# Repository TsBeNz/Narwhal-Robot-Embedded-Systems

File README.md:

# Module89-Frab5-G3
Electronics &amp; Embedded Systems

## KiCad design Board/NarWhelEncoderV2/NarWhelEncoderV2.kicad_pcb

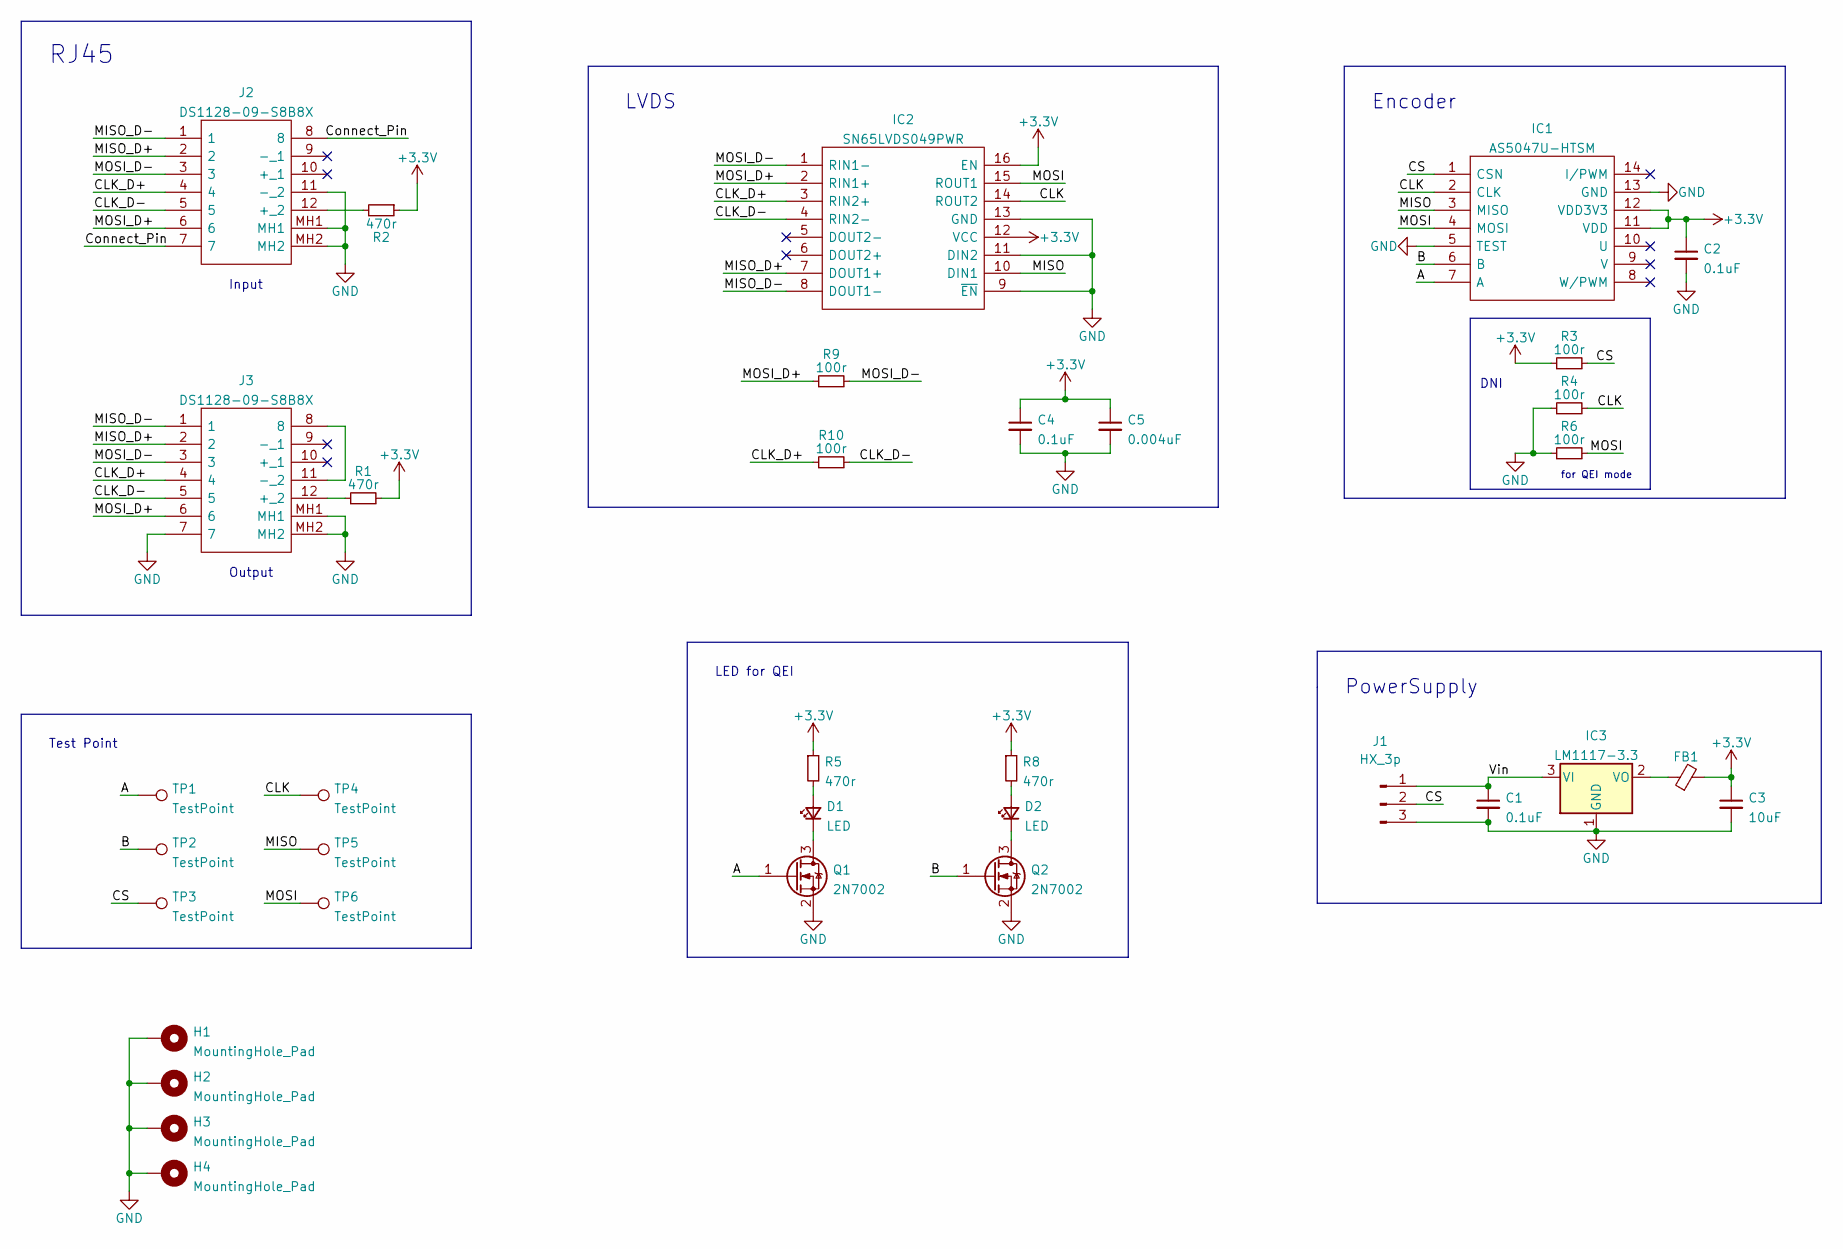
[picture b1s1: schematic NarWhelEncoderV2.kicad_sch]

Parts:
C1, C2, C4: 0.1uF; C_0603_1608Metric_Pad1.08x0.95mm_HandSolder
C3: 10uF; C_0603_1608Metric_Pad1.08x0.95mm_HandSolder
C5: 0.004uF; C_0603_1608Metric_Pad1.08x0.95mm_HandSolder
D1, D2: LED; LED_0603_1608Metric_Pad1.05x0.95mm_HandSolder
FB1: FerriteBead_Small; L_0603_1608Metric_Pad1.05x0.95mm_HandSolder
H1, H2, H3, H4: MountingHole_Pad; MountingHole_3.2mm_M3_Pad_Via
IC1: AS5047U-HTSM; SOP65P640X120-14N; Manufacturer_Part_Number AS5047U-HTSM; Mouser Part Number 985-AS5047U-HTSM
IC2: SN65LVDS049PWR; SOP65P640X120-16N; Manufacturer_Part_Number SN65LVDS049PWR; Mouser Part Number 595-SN65LVDS049PWR
IC3: LM1117-3.3; SOT-223-3_TabPin2
J1: HX_3p; JST_XH_B3B-XH-A_1x03_P2.50mm_Vertical
J2, J3: DS1128-09-S8B8X; DS112809S8B8X; Manufacturer_Part_Number DS1128-09-S8B8X
Q1, Q2: 2N7002; SOT-23_Handsoldering
R1, R2, R5, R8: 470r; R_0603_1608Metric_Pad0.98x0.95mm_HandSolder
R3, R4, R6, R9, R10: 100r; R_0603_1608Metric_Pad0.98x0.95mm_HandSolder
TP1, TP2, TP3, TP4, TP5, TP6: TestPoint; TestPoint_Pad_D1.5mm

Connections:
+3V3: C2.1, C3.1, C4.1, C5.1, FB1.2, IC1.11 (VDD), IC1.12 (VDD3V3), IC2.12 (VCC), IC2.16 (EN), R1.2, R2.1, R3.1, R5.1, R8.1
/A: IC1.7 (A), Q1.1 (G), TP1.1
/B: IC1.6 (B), Q2.1 (G), TP2.1
/CLK: IC1.2 (CLK), IC2.14 (ROUT2), R4.2, TP4.1
/CLK_D+: IC2.3 (RIN2+), J2.4, J3.4, R10.1
/CLK_D-: IC2.4 (RIN2-), J2.5, J3.5, R10.2
/CS: IC1.1 (CSN), J1.2, R3.2, TP3.1
/Connect_Pin: J2.7, J2.8
/MISO: IC1.3 (MISO), IC2.10 (DIN1), TP5.1
/MISO_D+: IC2.7 (DOUT1+), J2.2, J3.2
/MISO_D-: IC2.8 (DOUT1-), J2.1, J3.1
/MOSI: IC1.4 (MOSI), IC2.15 (ROUT1), R6.2, TP6.1
/MOSI_D+: IC2.2 (RIN1+), J2.6, J3.6, R9.1
/MOSI_D-: IC2.1 (RIN1-), J2.3, J3.3, R9.2
/Vin: C1.1, IC3.3 (VI), J1.1
GND: C1.2, C2.2, C3.2, C4.2, C5.2, H1.1, H2.1, H3.1, H4.1, IC1.5 (TEST), IC1.13 (GND), IC2.9 (~EN), IC2.11 (DIN2), IC2.13 (GND), IC3.1 (GND), J1.3, J2.11 (-_2), J2.MH1, J2.MH2, J3.7, J3.MH1, J3.MH2, Q1.2 (S), Q2.2 (S), R4.1, R6.1
unnamed: D1.1 (K), Q1.3 (D)
unnamed: D1.2 (A), R5.2
unnamed: D2.1 (K), Q2.3 (D)
unnamed: D2.2 (A), R8.2
unnamed: FB1.1, IC3.2 (VO)
unnamed: J2.12 (+_2), R2.2
unnamed: J3.8, J3.11 (-_2)
unnamed: J3.12 (+_2), R1.1

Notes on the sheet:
LED for QEI
Output
Test Point
Encoder
RJ45
Input
LVDS
PowerSupply
DNI
for QEI mode

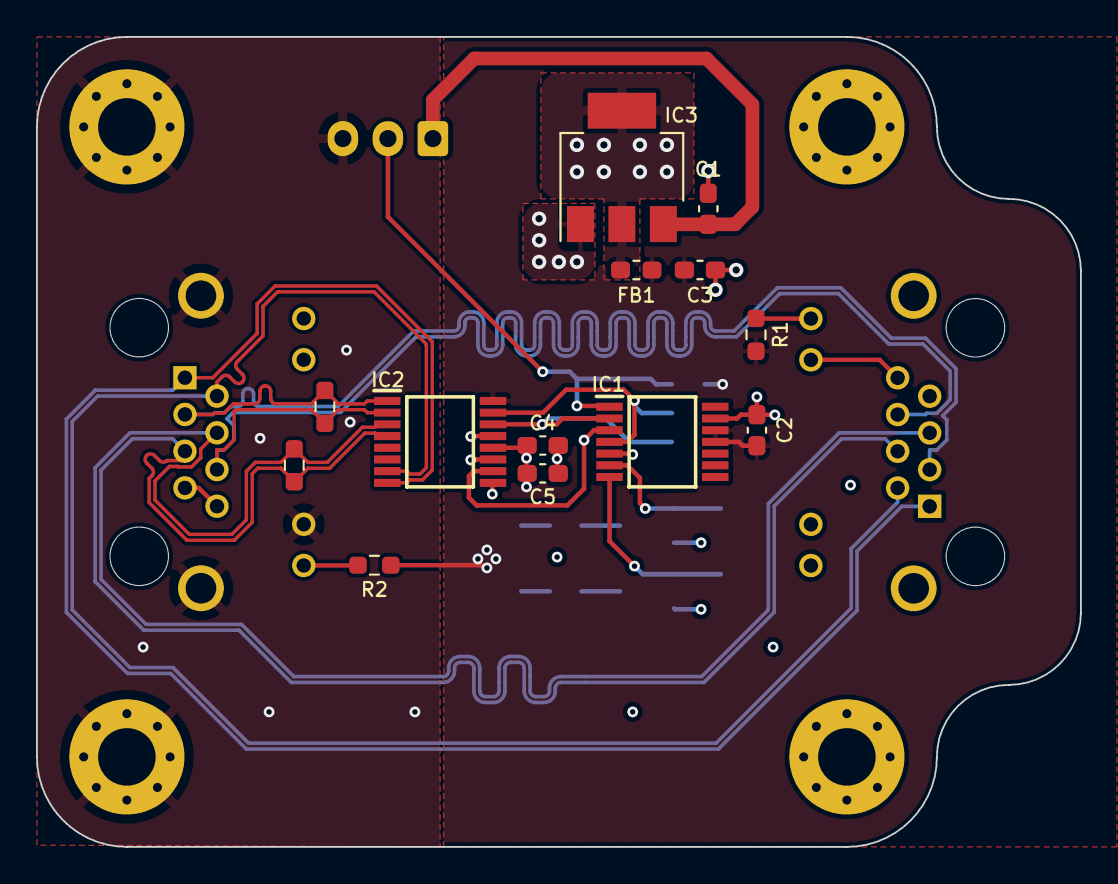
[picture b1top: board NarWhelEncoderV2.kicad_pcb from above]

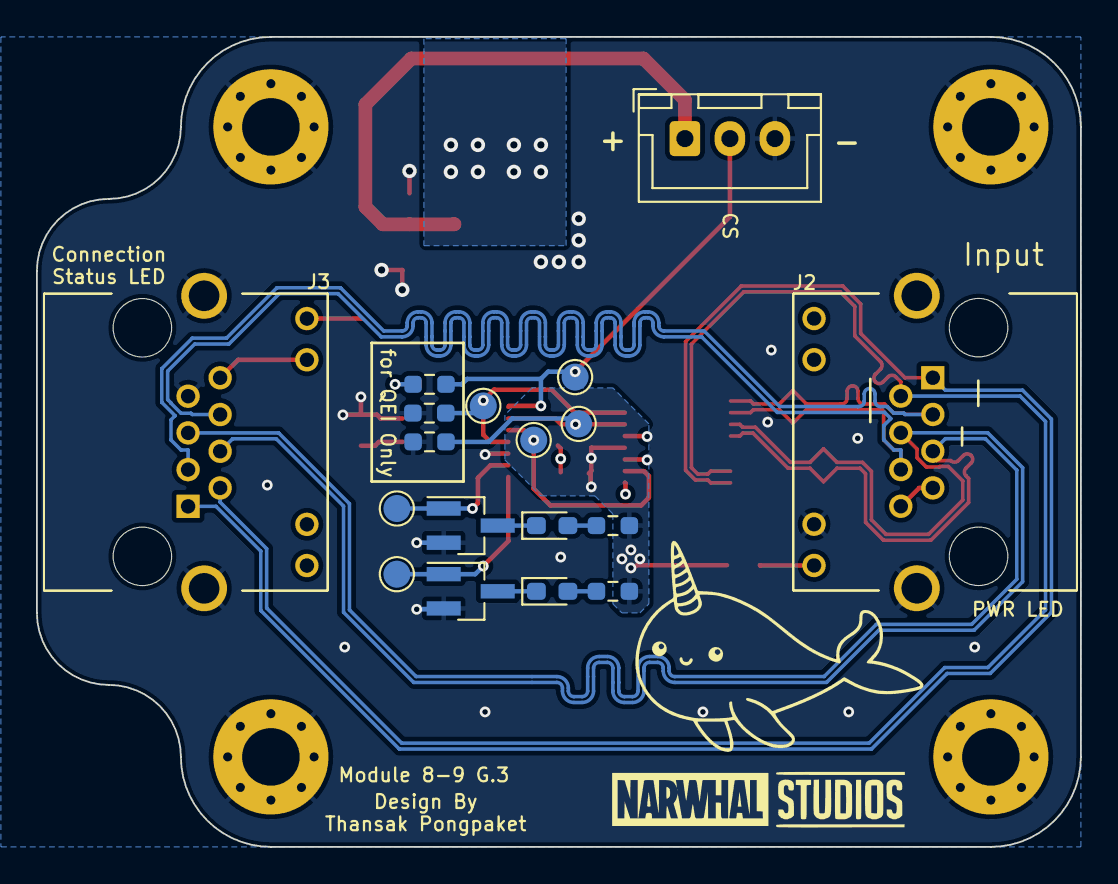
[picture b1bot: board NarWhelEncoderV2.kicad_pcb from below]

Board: 4 copper layers, 58.0 x 45.0 mm, 35 parts (18 on the bottom side), 24 nets.

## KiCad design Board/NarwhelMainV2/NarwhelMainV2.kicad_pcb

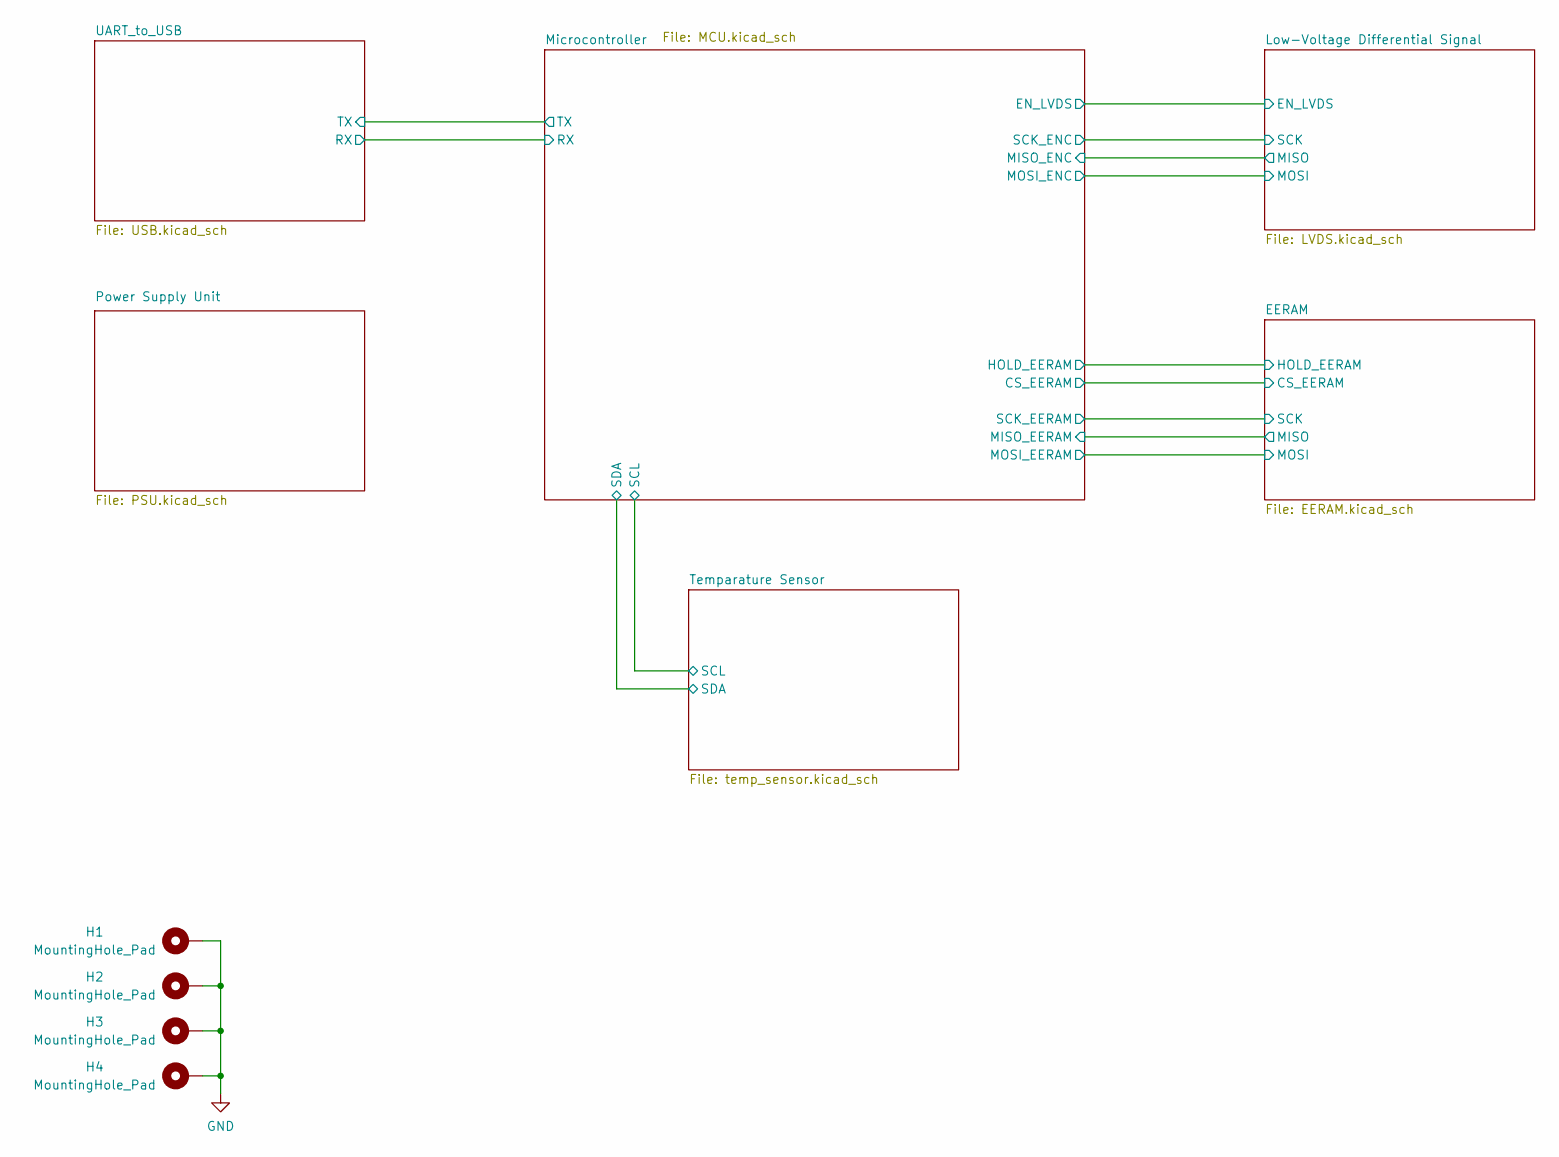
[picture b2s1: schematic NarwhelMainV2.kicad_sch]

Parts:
H1, H2, H3, H4: MountingHole_Pad; MountingHole_3.2mm_M3_Pad_Via

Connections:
GND: H1.1, H2.1, H3.1, H4.1; also elsewhere on the board

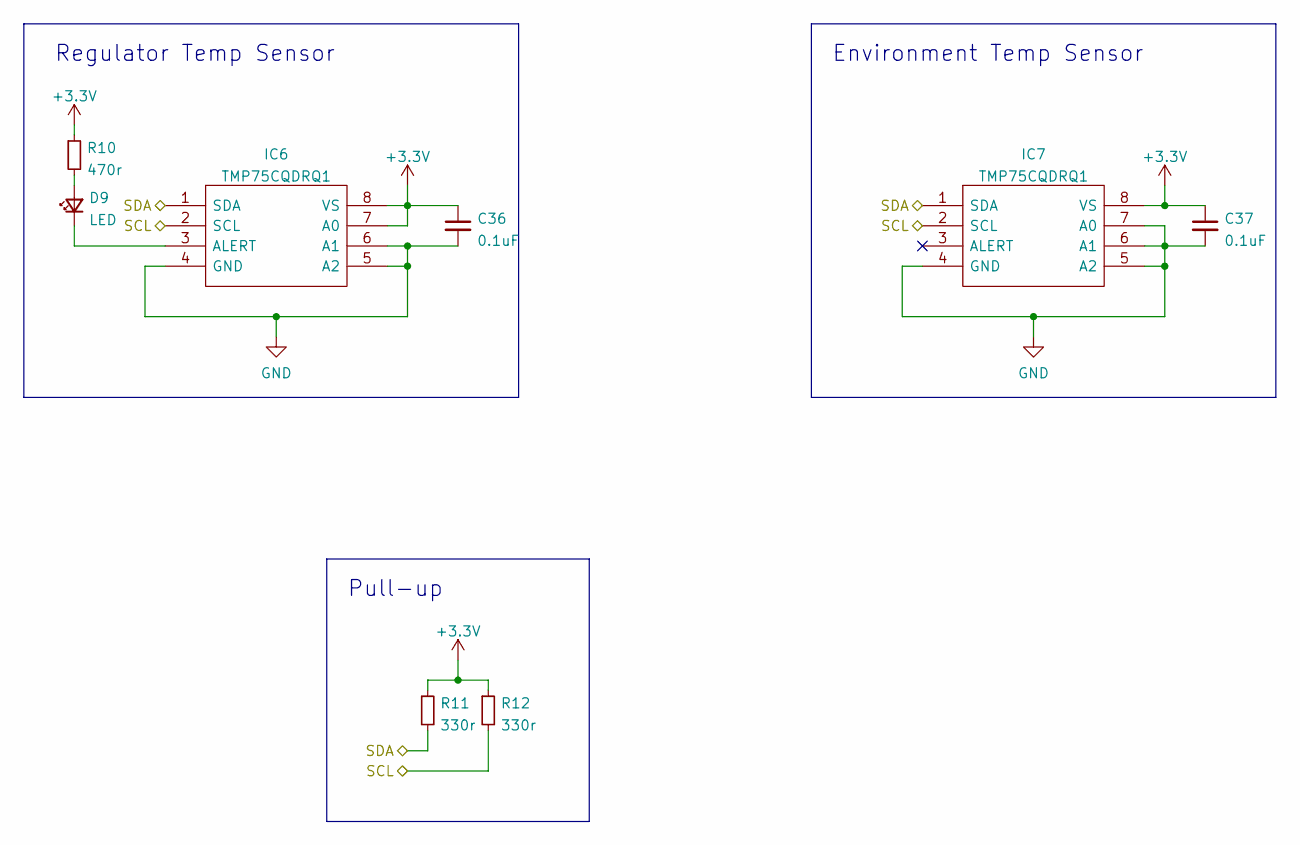
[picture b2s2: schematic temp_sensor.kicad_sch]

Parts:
C36, C37: 0.1uF; C_0603_1608Metric_Pad1.08x0.95mm_HandSolder
D9: LED; LED_0603_1608Metric_Pad1.05x0.95mm_HandSolder
IC6, IC7: TMP75CQDRQ1; SOIC127P600X175-8N; Manufacturer_Part_Number TMP75CQDRQ1; Mouser Part Number 595-TMP75CQDRQ1
R10: 470r; R_0603_1608Metric_Pad0.98x0.95mm_HandSolder
R11, R12: 330r; R_0603_1608Metric_Pad0.98x0.95mm_HandSolder

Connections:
+3V3: C36.1, C37.1, IC6.7 (A0), IC6.8 (VS), IC7.8 (VS), R10.1, R11.1, R12.1; also elsewhere on the board
/Microcontroller/SCL: IC6.2 (SCL), IC7.2 (SCL), R12.2; also elsewhere on the board
/Microcontroller/SDA: IC6.1 (SDA), IC7.1 (SDA), R11.2; also elsewhere on the board
GND: C36.2, C37.2, IC6.4 (GND), IC6.5 (A2), IC6.6 (A1), IC7.4 (GND), IC7.5 (A2), IC7.6 (A1), IC7.7 (A0); also elsewhere on the board
unnamed: D9.1 (K), IC6.3 (ALERT)
unnamed: D9.2 (A), R10.2

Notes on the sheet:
Regulator Temp Sensor
Environment Temp Sensor
Pull-up

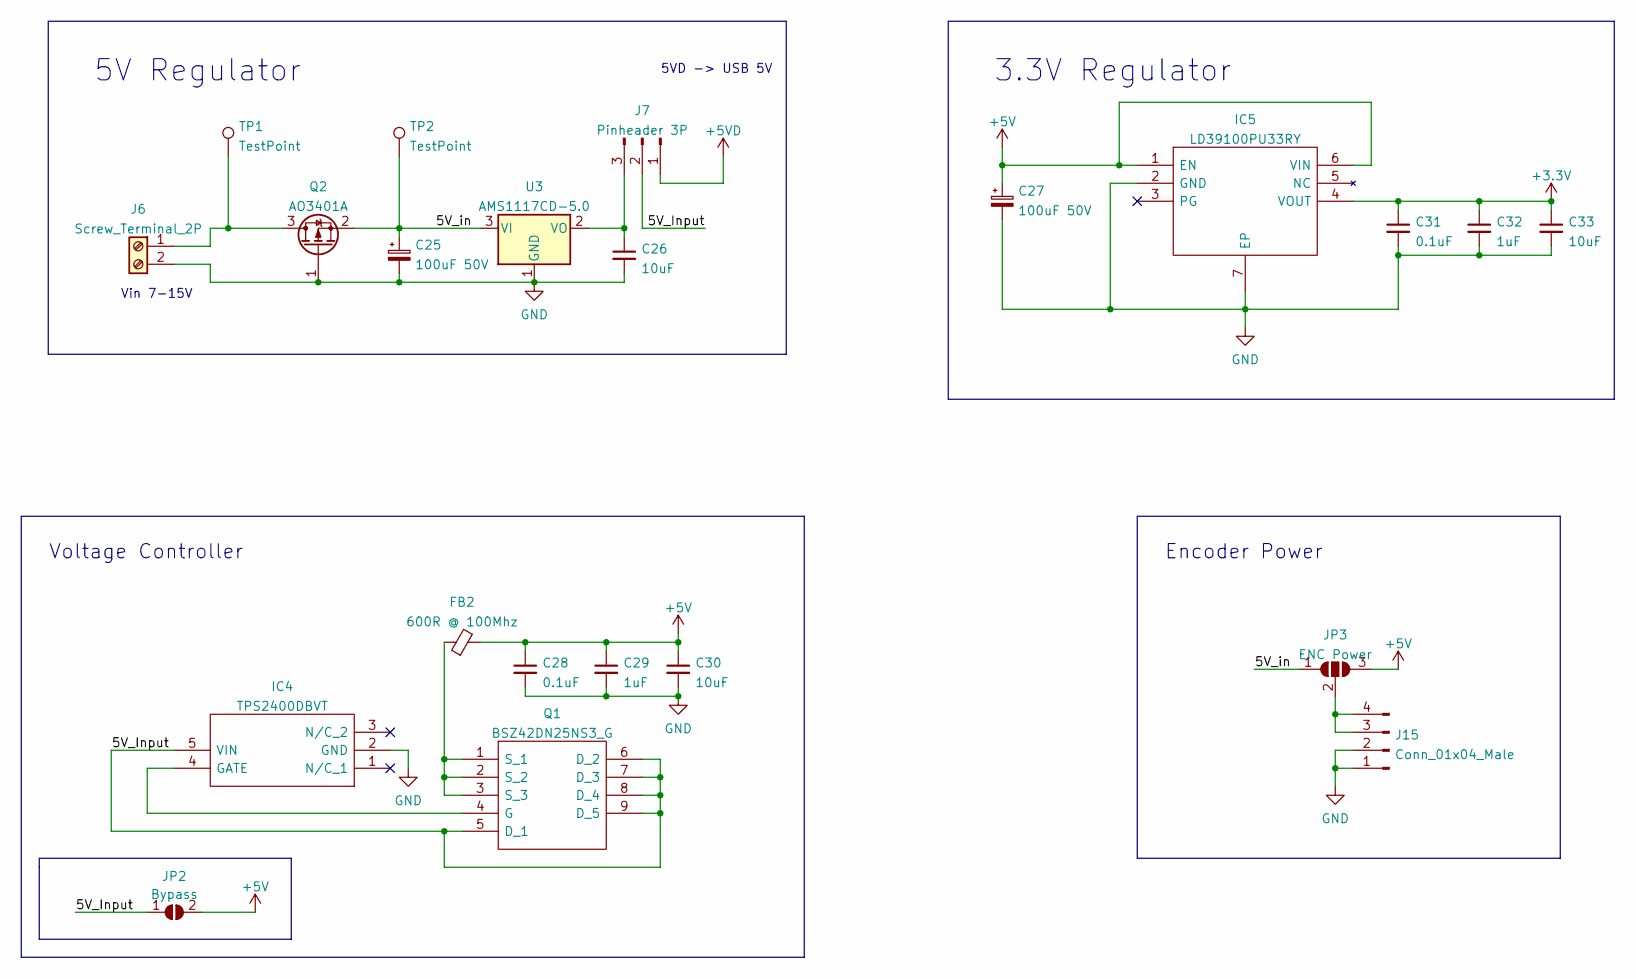
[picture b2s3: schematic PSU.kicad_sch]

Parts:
C25, C27: 100uF 50V; CP_Elec_6.3x5.4_Nichicon
C26, C30, C33: 10uF; C_0603_1608Metric_Pad1.08x0.95mm_HandSolder
C28, C31: 0.1uF; C_0603_1608Metric_Pad1.08x0.95mm_HandSolder
C29, C32: 1uF; C_0603_1608Metric_Pad1.08x0.95mm_HandSolder
FB2: 600R @ 100Mhz; L_0603_1608Metric_Pad1.05x0.95mm_HandSolder
IC4: TPS2400DBVT; SOT95P280X145-5N; Manufacturer_Part_Number TPS2400DBVT; Mouser Part Number 595-TPS2400DBVT
IC5: LD39100PU33RY; SON95P300X300X90-7N-D; Manufacturer_Part_Number LD39100PU33RY; Mouser Part Number 511-LD39100PU33RY
J6: Screw_Terminal_2P; TerminalBlock_Phoenix_MKDS-1,5-2_1x02_P5.00mm_Horizontal
J7: Pinheader 3P; PinHeader_1x03_P2.54mm_Vertical
J15: Conn_01x04_Male; JST_XH_B4B-XH-A_1x04_P2.50mm_Vertical
JP2: Bypass; SolderJumper-2_P1.3mm_Open_RoundedPad1.0x1.5mm
JP3: ENC Power; SolderJumper-3_P1.3mm_Open_RoundedPad1.0x1.5mm
Q1: BSZ42DN25NS3_G; BSZ42DN25NS3G; Manufacturer_Part_Number BSZ42DN25NS3 G; Mouser Part Number 726-BSZ42DN25NS3G
Q2: AO3401A; SOT-23
TP1, TP2: TestPoint; TestPoint_THTPad_D2.0mm_Drill1.0mm
U3: AMS1117CD-5.0; TO-252-3_TabPin2

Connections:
+3V3: C31.1, C32.1, C33.1, IC5.4 (VOUT); also elsewhere on the board
+5V: C27.1, C28.1, C29.1, C30.1, FB2.2, IC5.1 (EN), IC5.6 (VIN), JP2.2 (B), JP3.3 (B); also elsewhere on the board
+5VD: J7.1; also elsewhere on the board
/Power Supply Unit/5V_Input: IC4.5 (VIN), J7.2, JP2.1 (A), Q1.5 (D_1), Q1.6 (D_2), Q1.7 (D_3), Q1.8 (D_4), Q1.9 (D_5)
/Power Supply Unit/5V_in: C25.1, JP3.1 (A), Q2.2 (S), TP2.1, U3.3 (VI)
GND: C25.2, C26.2, C27.2, C28.2, C29.2, C30.2, C31.2, C32.2, C33.2, IC4.2 (GND), IC5.2 (GND), IC5.7 (EP), J6.2, J15.1, J15.2, Q2.1 (G), U3.1 (GND); also elsewhere on the board
unnamed: C26.1, J7.3, U3.2 (VO)
unnamed: FB2.1, Q1.1 (S_1), Q1.2 (S_2), Q1.3 (S_3)
unnamed: IC4.4 (GATE), Q1.4 (G)
unnamed: J6.1, Q2.3 (D), TP1.1
unnamed: J15.3, J15.4, JP3.2 (C)

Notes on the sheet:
5V Regulator
5VD -> USB 5V
Encoder Power
Voltage Controller
3.3V Regulator
Vin 7-15V

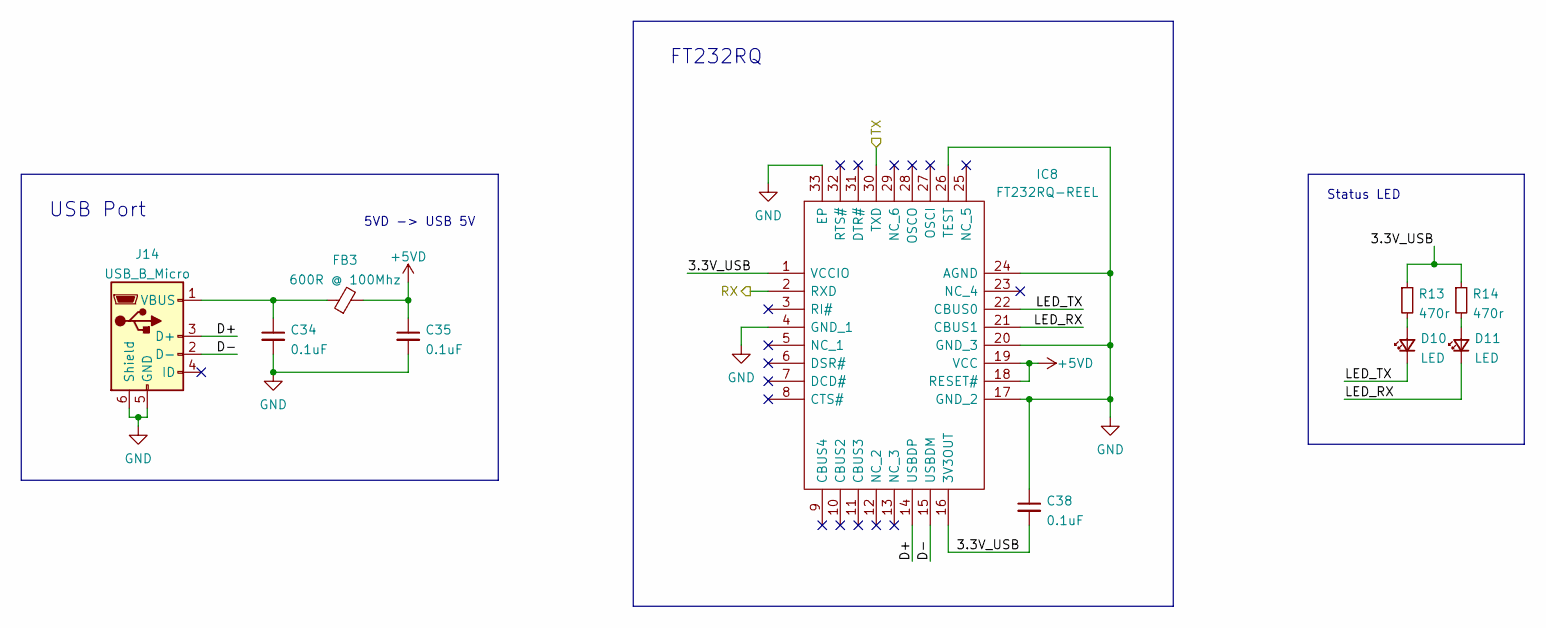
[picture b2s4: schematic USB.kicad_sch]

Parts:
C34, C35, C38: 0.1uF; C_0603_1608Metric_Pad1.08x0.95mm_HandSolder
D10, D11: LED; LED_0603_1608Metric_Pad1.05x0.95mm_HandSolder
FB3: 600R @ 100Mhz; L_0603_1608Metric_Pad1.05x0.95mm_HandSolder
IC8: FT232RQ-REEL; QFN50P500X500X90-33N-D; Manufacturer_Part_Number FT232RQ-REEL; Mouser Part Number 895-FT232RQ
J14: USB_B_Micro; USB_Micro-B_Molex_47346-0001
R13, R14: 470r; R_0603_1608Metric_Pad0.98x0.95mm_HandSolder

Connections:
+5VD: C35.1, FB3.2, IC8.18 (RESET#), IC8.19 (VCC); also elsewhere on the board
/Microcontroller/RX: IC8.2 (RXD); also elsewhere on the board
/Microcontroller/TX: IC8.30 (TXD); also elsewhere on the board
/UART_to_USB/3.3V_USB: C38.2, IC8.1 (VCCIO), IC8.16 (3V3OUT), R13.1, R14.1
/UART_to_USB/D+: IC8.14 (USBDP), J14.3 (D+)
/UART_to_USB/D-: IC8.15 (USBDM), J14.2 (D-)
/UART_to_USB/LED_RX: D11.1 (K), IC8.21 (CBUS1)
/UART_to_USB/LED_TX: D10.1 (K), IC8.22 (CBUS0)
GND: C34.2, C35.2, C38.1, IC8.4 (GND_1), IC8.17 (GND_2), IC8.20 (GND_3), IC8.24 (AGND), IC8.26 (TEST), IC8.33 (EP), J14.5 (GND), J14.6 (Shield); also elsewhere on the board
unnamed: C34.1, FB3.1, J14.1 (VBUS)
unnamed: D10.2 (A), R13.2
unnamed: D11.2 (A), R14.2

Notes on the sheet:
FT232RQ
5VD -> USB 5V
Status LED
USB Port

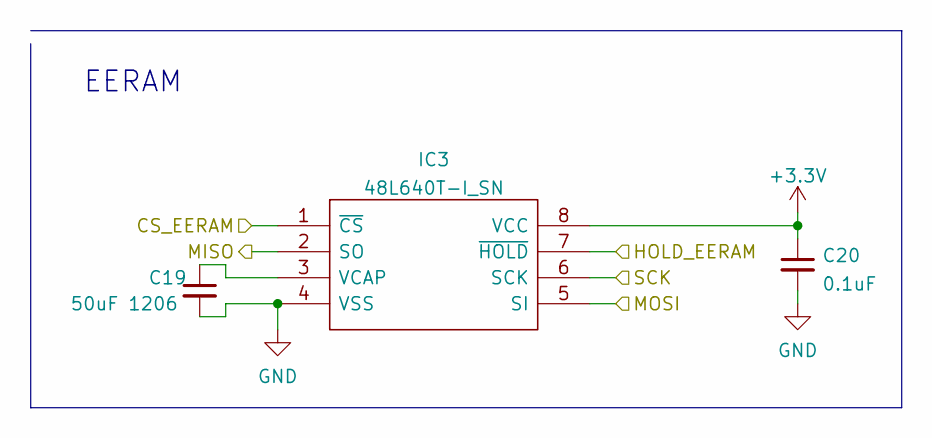
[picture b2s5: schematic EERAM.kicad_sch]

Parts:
C19: 50uF 1206; C_1206_3216Metric_Pad1.33x1.80mm_HandSolder
C20: 0.1uF; C_0603_1608Metric_Pad1.08x0.95mm_HandSolder
IC3: 48L640T-I_SN; SOIC127P600X175-8N; Manufacturer_Part_Number 48L640T-I/SN; Mouser Part Number 579-48L640T-I/SN

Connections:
+3V3: C20.1, IC3.8 (VCC); also elsewhere on the board
/EERAM/CS_EERAM: IC3.1 (~CS); also elsewhere on the board
/EERAM/HOLD_EERAM: IC3.7 (~HOLD); also elsewhere on the board
/EERAM/MISO: IC3.2 (SO); also elsewhere on the board
/EERAM/MOSI: IC3.5 (SI); also elsewhere on the board
/EERAM/SCK: IC3.6 (SCK); also elsewhere on the board
GND: C19.2, C20.2, IC3.4 (VSS); also elsewhere on the board
unnamed: C19.1, IC3.3 (VCAP)

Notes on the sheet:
EERAM

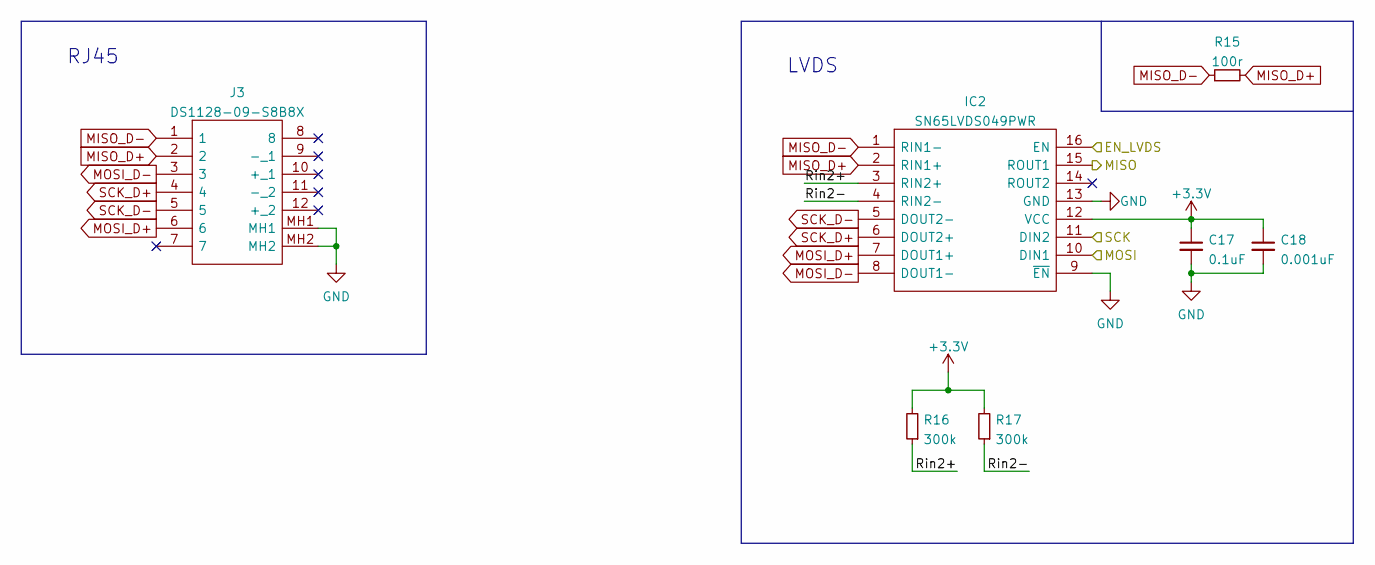
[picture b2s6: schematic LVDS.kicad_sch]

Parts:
C17: 0.1uF; C_0603_1608Metric_Pad1.08x0.95mm_HandSolder
C18: 0.001uF; C_0603_1608Metric_Pad1.08x0.95mm_HandSolder
IC2: SN65LVDS049PWR; SOP65P640X120-16N; Manufacturer_Part_Number SN65LVDS049PWR; Mouser Part Number 595-SN65LVDS049PWR
J3: DS1128-09-S8B8X; DS112809S8B8X; Manufacturer_Part_Number DS1128-09-S8B8X
R15: 100r; R_0603_1608Metric_Pad0.98x0.95mm_HandSolder
R16, R17: 300k; R_0402_1005Metric_Pad0.72x0.64mm_HandSolder

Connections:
+3V3: C17.1, C18.1, IC2.12 (VCC), R16.2, R17.2; also elsewhere on the board
/Low-Voltage Differential Signal/EN_LVDS: IC2.16 (EN); also elsewhere on the board
/Low-Voltage Differential Signal/MISO: IC2.15 (ROUT1); also elsewhere on the board
/Low-Voltage Differential Signal/MOSI: IC2.10 (DIN1); also elsewhere on the board
/Low-Voltage Differential Signal/Rin2+: IC2.3 (RIN2+), R16.1
/Low-Voltage Differential Signal/Rin2-: IC2.4 (RIN2-), R17.1
/Low-Voltage Differential Signal/SCK: IC2.11 (DIN2); also elsewhere on the board
GND: C17.2, C18.2, IC2.9 (~EN), IC2.13 (GND), J3.MH1, J3.MH2; also elsewhere on the board
MISO_D+: IC2.2 (RIN1+), J3.2, R15.2
MISO_D-: IC2.1 (RIN1-), J3.1, R15.1
MOSI_D+: IC2.7 (DOUT1+), J3.6
MOSI_D-: IC2.8 (DOUT1-), J3.3
SCK_D+: IC2.6 (DOUT2+), J3.4
SCK_D-: IC2.5 (DOUT2-), J3.5

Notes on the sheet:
RJ45
LVDS

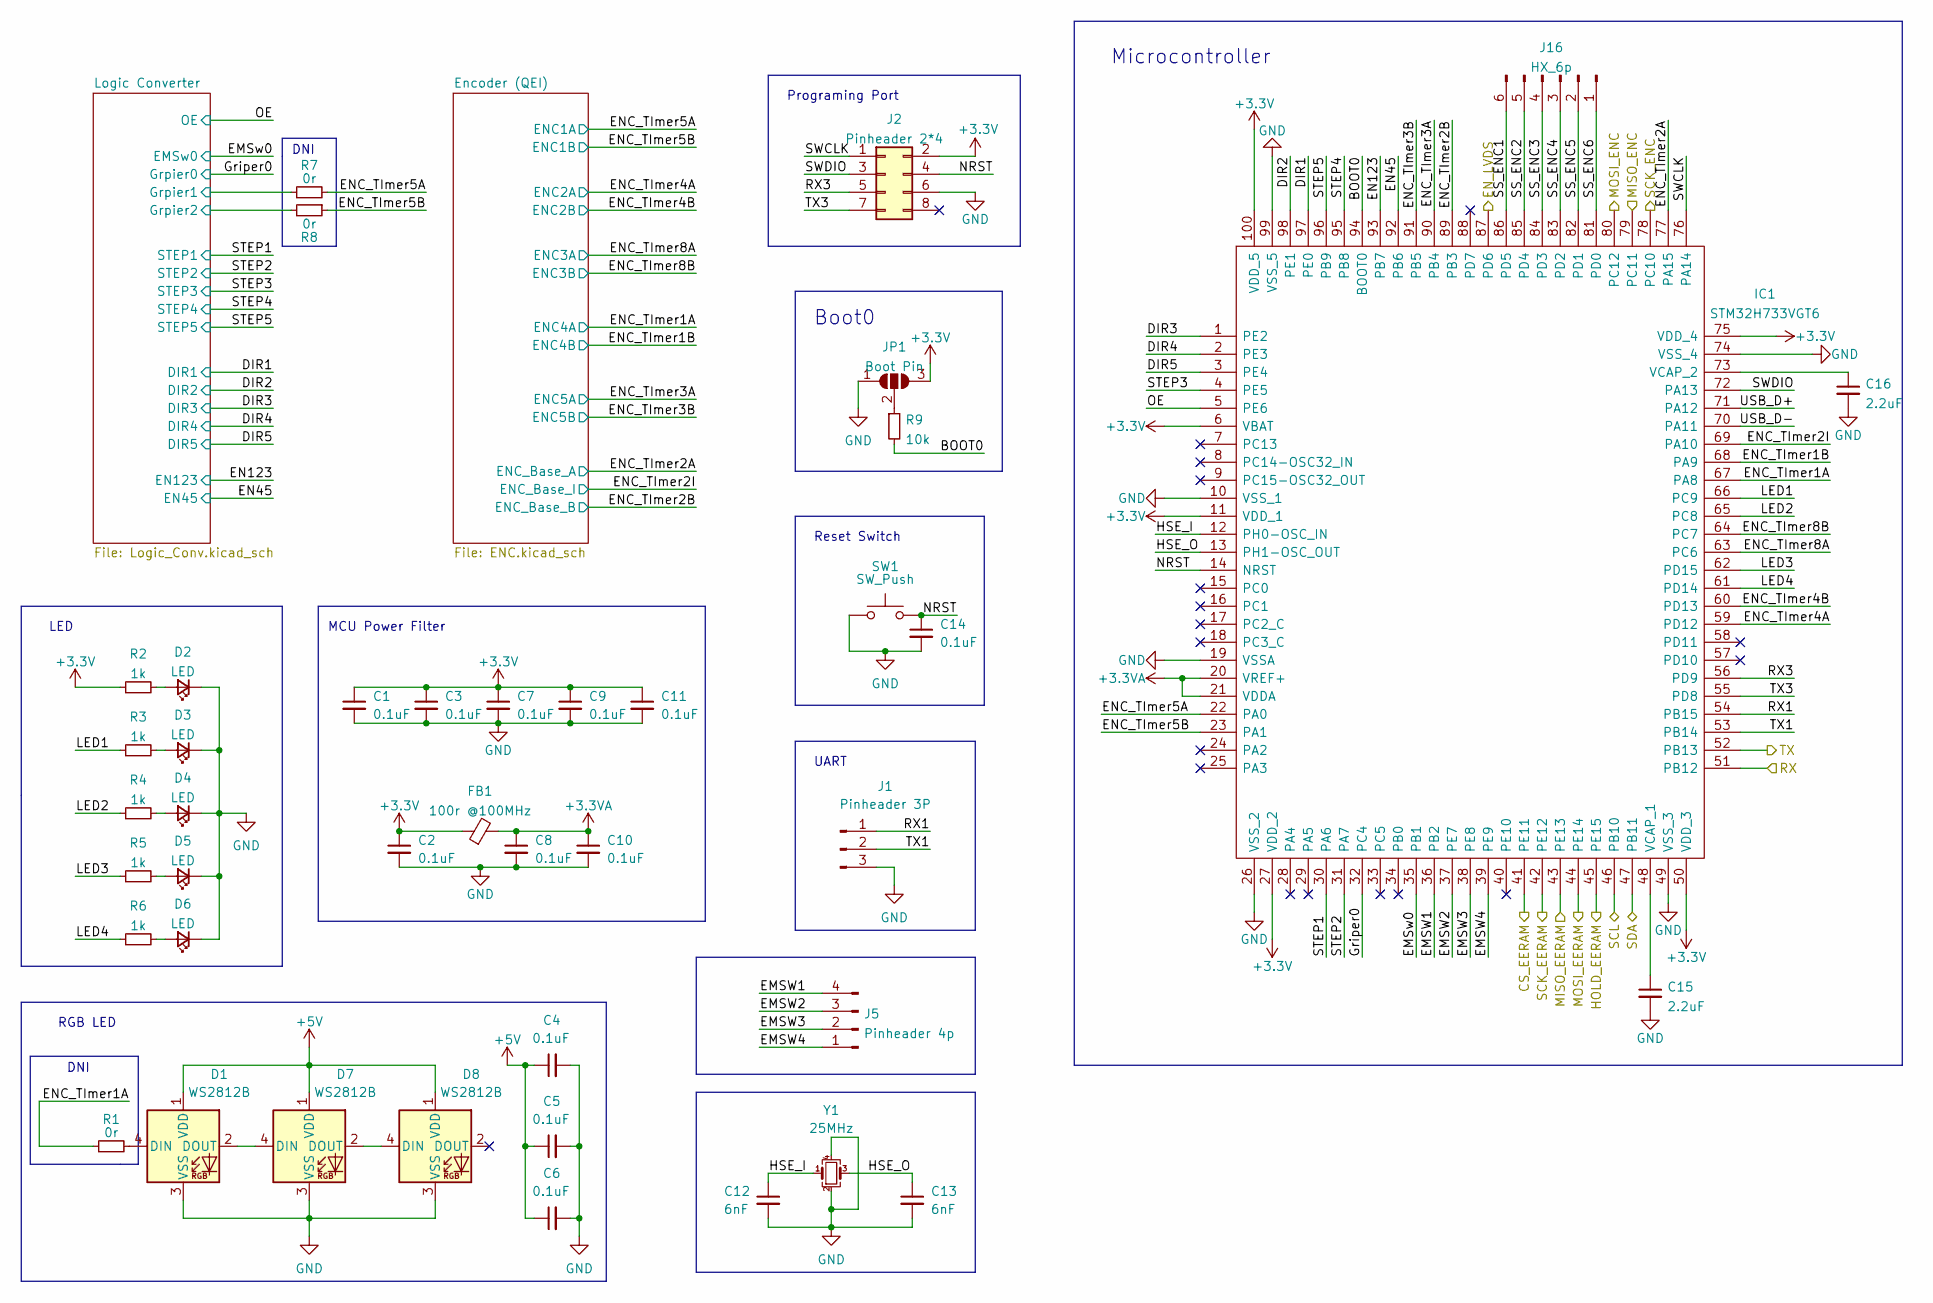
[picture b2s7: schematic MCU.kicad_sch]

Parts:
C1, C2, C3, C4, C5, C6, C7, C8, C9, C10, C11, C14: 0.1uF; C_0603_1608Metric_Pad1.08x0.95mm_HandSolder
C12, C13: 6nF; C_0603_1608Metric_Pad1.08x0.95mm_HandSolder
C15, C16: 2.2uF; C_0603_1608Metric_Pad1.08x0.95mm_HandSolder
D1, D7, D8: WS2812B; LED_WS2812B_PLCC4_5.0x5.0mm_P3.2mm
D2, D3, D4, D5, D6: LED; LED_0603_1608Metric_Pad1.05x0.95mm_HandSolder
FB1: 100r @100MHz; L_0603_1608Metric_Pad1.05x0.95mm_HandSolder
IC1: STM32H733VGT6; QFP50P1600X1600X160-100N; Manufacturer_Part_Number STM32H733VGT6; Mouser Part Number 511-STM32H733VGT6
J1: Pinheader 3P; PinHeader_1x03_P2.54mm_Vertical
J2: Pinheader 2*4; PinHeader_2x04_P2.54mm_Vertical
J5: Pinheader 4p; PinHeader_1x04_P2.54mm_Vertical
J16: HX_6p; JST_XH_B6B-XH-A_1x06_P2.50mm_Vertical
JP1: Boot Pin; SolderJumper-3_P2.0mm_Open_TrianglePad1.0x1.5mm
R1, R7, R8: 0r; R_0603_1608Metric_Pad0.98x0.95mm_HandSolder
R2, R3, R4, R5, R6: 1k; R_0603_1608Metric_Pad0.98x0.95mm_HandSolder
R9: 10k; R_0603_1608Metric_Pad0.98x0.95mm_HandSolder
SW1: SW_Push; SW_SPST_CK_RS282G05A3
Y1: 25MHz; Crystal_SMD_SeikoEpson_FA238-4Pin_3.2x2.5mm

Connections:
+3.3VA: C8.1, C10.1, FB1.2, IC1.20 (VREF+), IC1.21 (VDDA)
+3V3: C1.1, C2.1, C3.1, C7.1, C9.1, C11.1, FB1.1, IC1.6 (VBAT), IC1.11 (VDD_1), IC1.27 (VDD_2), IC1.50 (VDD_3), IC1.75 (VDD_4), IC1.100 (VDD_5), J2.2, JP1.3 (B), R2.1; also elsewhere on the board
+5V: C4.1, C5.1, C6.1, D1.1 (VDD), D7.1 (VDD), D8.1 (VDD); also elsewhere on the board
/EERAM/CS_EERAM: IC1.41 (PE11); also elsewhere on the board
/EERAM/HOLD_EERAM: IC1.45 (PE15); also elsewhere on the board
/EERAM/MISO: IC1.43 (PE13); also elsewhere on the board
/EERAM/MOSI: IC1.44 (PE14); also elsewhere on the board
/EERAM/SCK: IC1.42 (PE12); also elsewhere on the board
/Low-Voltage Differential Signal/EN_LVDS: IC1.87 (PD6); also elsewhere on the board
/Low-Voltage Differential Signal/MISO: IC1.79 (PC11); also elsewhere on the board
/Low-Voltage Differential Signal/MOSI: IC1.80 (PC12); also elsewhere on the board
/Low-Voltage Differential Signal/SCK: IC1.78 (PC10); also elsewhere on the board
/Microcontroller/BOOT0: IC1.94 (BOOT0), R9.2
/Microcontroller/DIR1: IC1.97 (PE0); also elsewhere on the board
/Microcontroller/DIR2: IC1.98 (PE1); also elsewhere on the board
/Microcontroller/DIR3: IC1.1 (PE2); also elsewhere on the board
/Microcontroller/DIR4: IC1.2 (PE3); also elsewhere on the board
/Microcontroller/DIR5: IC1.3 (PE4); also elsewhere on the board
/Microcontroller/EMSW1: IC1.36 (PB2), J5.4
/Microcontroller/EMSW2: IC1.37 (PE7), J5.3
/Microcontroller/EMSW3: IC1.38 (PE8), J5.2
/Microcontroller/EMSW4: IC1.39 (PE9), J5.1
/Microcontroller/EMSw0: IC1.35 (PB1); also elsewhere on the board
/Microcontroller/EN45: IC1.92 (PB6); also elsewhere on the board
/Microcontroller/EN123: IC1.93 (PB7); also elsewhere on the board
/Microcontroller/ENC_TImer1A: IC1.67 (PA8), R1.1; also elsewhere on the board
/Microcontroller/ENC_TImer1B: IC1.68 (PA9); also elsewhere on the board
/Microcontroller/ENC_TImer2A: IC1.77 (PA15); also elsewhere on the board
/Microcontroller/ENC_TImer2B: IC1.89 (PB3); also elsewhere on the board
/Microcontroller/ENC_TImer2I: IC1.69 (PA10); also elsewhere on the board
/Microcontroller/ENC_TImer3A: IC1.90 (PB4); also elsewhere on the board
/Microcontroller/ENC_TImer3B: IC1.91 (PB5); also elsewhere on the board
/Microcontroller/ENC_TImer4A: IC1.59 (PD12); also elsewhere on the board
/Microcontroller/ENC_TImer4B: IC1.60 (PD13); also elsewhere on the board
/Microcontroller/ENC_TImer5A: IC1.22 (PA0), R7.2; also elsewhere on the board
/Microcontroller/ENC_TImer5B: IC1.23 (PA1), R8.1; also elsewhere on the board
/Microcontroller/ENC_TImer8A: IC1.63 (PC6); also elsewhere on the board
/Microcontroller/ENC_TImer8B: IC1.64 (PC7); also elsewhere on the board
/Microcontroller/Griper0: IC1.32 (PC4); also elsewhere on the board
/Microcontroller/HSE_I: C12.1, IC1.12 (PH0-OSC_IN), Y1.1
/Microcontroller/HSE_O: C13.1, IC1.13 (PH1-OSC_OUT), Y1.3
/Microcontroller/LED1: IC1.66 (PC9), R3.1
/Microcontroller/LED2: IC1.65 (PC8), R4.1
/Microcontroller/LED3: IC1.62 (PD15), R5.1
/Microcontroller/LED4: IC1.61 (PD14), R6.1
/Microcontroller/Logic Converter/Grpier1: R7.1; also elsewhere on the board
/Microcontroller/Logic Converter/Grpier2: R8.2; also elsewhere on the board
/Microcontroller/NRST: C14.1, IC1.14 (NRST), J2.4, SW1.2
/Microcontroller/OE: IC1.5 (PE6); also elsewhere on the board
/Microcontroller/RX: IC1.51 (PB12); also elsewhere on the board
/Microcontroller/RX1: IC1.54 (PB15), J1.1
/Microcontroller/RX3: IC1.56 (PD9), J2.5
/Microcontroller/SCL: IC1.46 (PB10); also elsewhere on the board
/Microcontroller/SDA: IC1.47 (PB11); also elsewhere on the board
/Microcontroller/SS_ENC1: IC1.86 (PD5), J16.6
/Microcontroller/SS_ENC2: IC1.85 (PD4), J16.5
/Microcontroller/SS_ENC3: IC1.84 (PD3), J16.4
/Microcontroller/SS_ENC4: IC1.83 (PD2), J16.3
/Microcontroller/SS_ENC5: IC1.82 (PD1), J16.2
/Microcontroller/SS_ENC6: IC1.81 (PD0), J16.1
/Microcontroller/STEP1: IC1.30 (PA6); also elsewhere on the board
/Microcontroller/STEP2: IC1.31 (PA7); also elsewhere on the board
/Microcontroller/STEP3: IC1.4 (PE5); also elsewhere on the board
/Microcontroller/STEP4: IC1.95 (PB8); also elsewhere on the board
/Microcontroller/STEP5: IC1.96 (PB9); also elsewhere on the board
/Microcontroller/SWCLK: IC1.76 (PA14), J2.1
/Microcontroller/SWDIO: IC1.72 (PA13), J2.3
/Microcontroller/TX: IC1.52 (PB13); also elsewhere on the board
/Microcontroller/TX1: IC1.53 (PB14), J1.2
/Microcontroller/TX3: IC1.55 (PD8), J2.7
/Microcontroller/USB_D+: IC1.71 (PA12)
/Microcontroller/USB_D-: IC1.70 (PA11)
GND: C1.2, C2.2, C3.2, C4.2, C5.2, C6.2, C7.2, C8.2, C9.2, C10.2, C11.2, C12.2, C13.2, C14.2, C15.2, C16.2, D1.3 (VSS), D2.1 (K), D3.1 (K), D4.1 (K), D5.1 (K), D6.1 (K), D7.3 (VSS), D8.3 (VSS), IC1.10 (VSS_1), IC1.19 (VSSA), IC1.26 (VSS_2), IC1.49 (VSS_3), IC1.74 (VSS_4), IC1.99 (VSS_5), J1.3, J2.6, JP1.1 (A), SW1.1, Y1.2, Y1.4; also elsewhere on the board
unnamed: C15.1, IC1.48 (VCAP_1)
unnamed: C16.1, IC1.73 (VCAP_2)
unnamed: D1.2 (DOUT), D7.4 (DIN)
unnamed: D1.4 (DIN), R1.2
unnamed: D2.2 (A), R2.2
unnamed: D3.2 (A), R3.2
unnamed: D4.2 (A), R4.2
unnamed: D5.2 (A), R5.2
unnamed: D6.2 (A), R6.2
unnamed: D7.2 (DOUT), D8.4 (DIN)
unnamed: JP1.2 (C), R9.1

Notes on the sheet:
LED
Reset Switch
DNI
RGB LED
Boot0
Programing Port
UART
Microcontroller
MCU Power Filter
